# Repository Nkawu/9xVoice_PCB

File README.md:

Circuit board designs for the 9X RC Transmitters mods

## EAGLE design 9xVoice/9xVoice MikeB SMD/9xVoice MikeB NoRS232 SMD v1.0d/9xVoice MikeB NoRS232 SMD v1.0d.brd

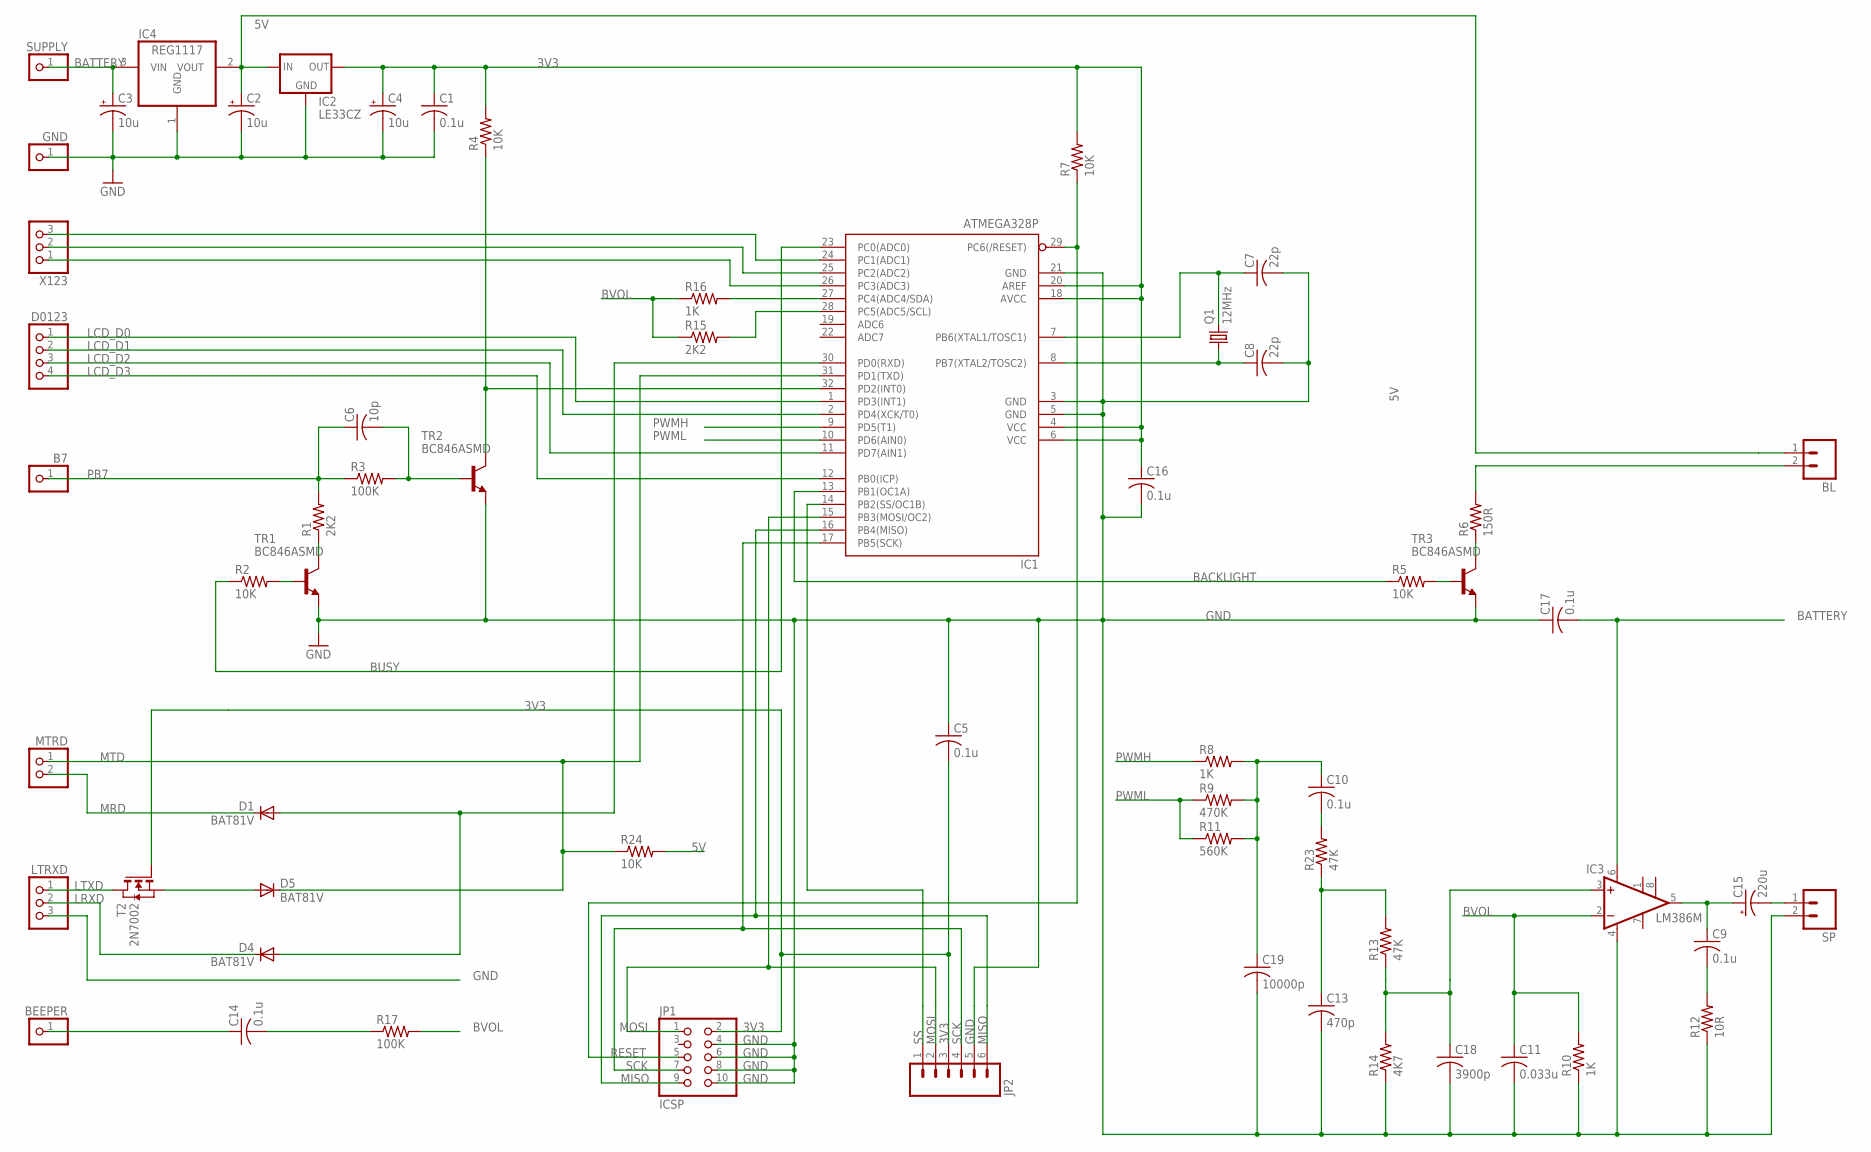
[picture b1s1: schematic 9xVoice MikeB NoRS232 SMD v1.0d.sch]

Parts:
B7: PINHD-1X1; 1X01
BEEPER: PINHD-1X1; 1X01
BL: M02PTH; 1X02
C1, C5, C9, C10, C14, C16, C17: 0.1u; C1206
C2, C3, C4: 10u; A/3216-18R
C6: 10p; C1206
C7, C8: 22p; C1206
C11: 0.033u; C1206
C13: 470p; C1206
C15: 220u; CT7343
C18: 3900p; C1206
C19: 10000p; C1206
D1, D4, D5: BAT81V; SOD123
D0123: PINHD-1X4; 1X04
GND: PINHD-1X1; 1X01
IC1: ATMEGA328P; TQFP32-08; MPN ATMEGA8-16AU
IC2: LE33CZ; SOT23
IC3: LM386M; SO08
IC4: REG1117; SOT223
JP1: ICSP; 2X05
JP2: M06SIP; 1X06
LTRXD: PINHD-1X3; 1X03
MTRD: PINHD-1X2; 1X02
Q1: 12MHz; 2-SMD
R1, R15: 2K2; R1206
R2, R4, R5, R7, R24: 10K; R1206
R3, R17: 100K; R1206
R6: 150R; R1206
R8, R10, R16: 1K; R1206
R9: 470K; R1206
R11: 560K; R1206
R12: 10R; R1206
R13, R23: 47K; R1206
R14: 4K7; R1206
SP: M02PTH; 1X02
SUPPLY: PINHD-1X1; 1X01
T2: 2N7002; SOT-23
TR1, TR2, TR3: BC846ASMD; SOT23
X123: PINHD-1X3; 1X03

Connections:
3V3: C1.1, C4.+, C5.2, C16.1, IC1.4 (VCC), IC1.6 (VCC), IC1.18 (AVCC), IC1.20 (AREF), IC2.2 (OUT), JP1.2, JP2.3, R4.2, R7.2, T2.3 (G)
5V: BL.1, C2.+, IC2.3 (IN), IC4.2 (VOUT), R24.2
BACKLIGHT: IC1.13 (PB1(OC1A)), R5.1
BATTERY: C3.+, C17.2, IC3.6 (VS), IC4.3 (VIN), SUPPLY.1
BEEPER: BEEPER.1, C14.1
BUSY: IC1.23 (PC0(ADC0)), R2.1
BVOL: C11.1, IC3.2 (-IN), R10.2, R15.1, R16.1, R17.2
GND: C1.2, C2.-, C3.-, C4.-, C5.1, C7.2, C8.2, C11.2, C13.2, C16.2, C17.1, C18.2, C19.2, GND.1, IC1.3 (GND), IC1.5 (GND), IC1.21 (GND), IC2.1 (GND), IC3.4 (GND), IC4.1 (GND), JP1.4, JP1.6, JP1.8, JP1.10, JP2.5, LTRXD.3, R10.1, R12.1, R14.1, SP.2, TR1.2 (E), TR2.2 (E), TR3.2 (E)
LCD_D0: D0123.1, IC1.1 (PD3(INT1))
LCD_D1: D0123.2, IC1.2 (PD4(XCK/T0))
LCD_D2: D0123.3, IC1.11 (PD7(AIN1))
LCD_D3: D0123.4, IC1.12 (PB0(ICP))
LRXD: D4.C, LTRXD.2
LTXD: LTRXD.1, T2.1 (D)
MISO: IC1.16 (PB4(MISO)), JP1.9, JP2.6
MOSI: IC1.15 (PB3(MOSI/OC2)), JP1.1, JP2.2
MRD: D1.C, MTRD.2
MTD: D5.C, IC1.31 (PD1(TXD)), MTRD.1, R24.1
unnamed: C13.1, R13.2, R23.1
unnamed: IC1.28 (PC5(ADC5/SCL)), R15.2
unnamed: IC1.27 (PC4(ADC4/SDA)), R16.2
unnamed: D5.A, T2.2 (S)
unnamed: R1.1, TR1.3 (C)
unnamed: R2.2, TR1.1 (B)
unnamed: C6.2, R3.2, TR2.1 (B)
unnamed: C14.2, R17.1
unnamed: R5.2, TR3.1 (B)
unnamed: R6.1, TR3.3 (C)
unnamed: C10.2, R23.2
unnamed: IC1.32 (PD2(INT0)), R4.1, TR2.3 (C)
unnamed: C8.1, IC1.8 (PB7(XTAL2/TOSC2)), Q1.P$1 (1)
unnamed: C7.1, IC1.7 (PB6(XTAL1/TOSC1)), Q1.P$2 (2)
unnamed: BL.2, R6.2
unnamed: C9.1, C15.+, IC3.5 (OUT)
unnamed: C9.2, R12.2
unnamed: C15.-, SP.1
unnamed: C10.1, C19.1, R8.2, R9.2, R11.2
unnamed: C18.1, IC3.3 (+IN), R13.1, R14.2
PB7: B7.1, C6.1, R1.2, R3.1
PWMH: IC1.9 (PD5(T1)), R8.1
PWML: IC1.10 (PD6(AIN0)), R9.1, R11.1
RESET: IC1.29 (PC6(/RESET)), JP1.5, R7.1
RXD: D1.A, D4.A, IC1.30 (PD0(RXD))
SCK: IC1.17 (PB5(SCK)), JP1.7, JP2.4
SS: IC1.14 (PB2(SS/OC1B)), JP2.1
X1: IC1.26 (PC3(ADC3)), X123.1
X2: IC1.25 (PC2(ADC2)), X123.2
X3: IC1.24 (PC1(ADC1)), X123.3

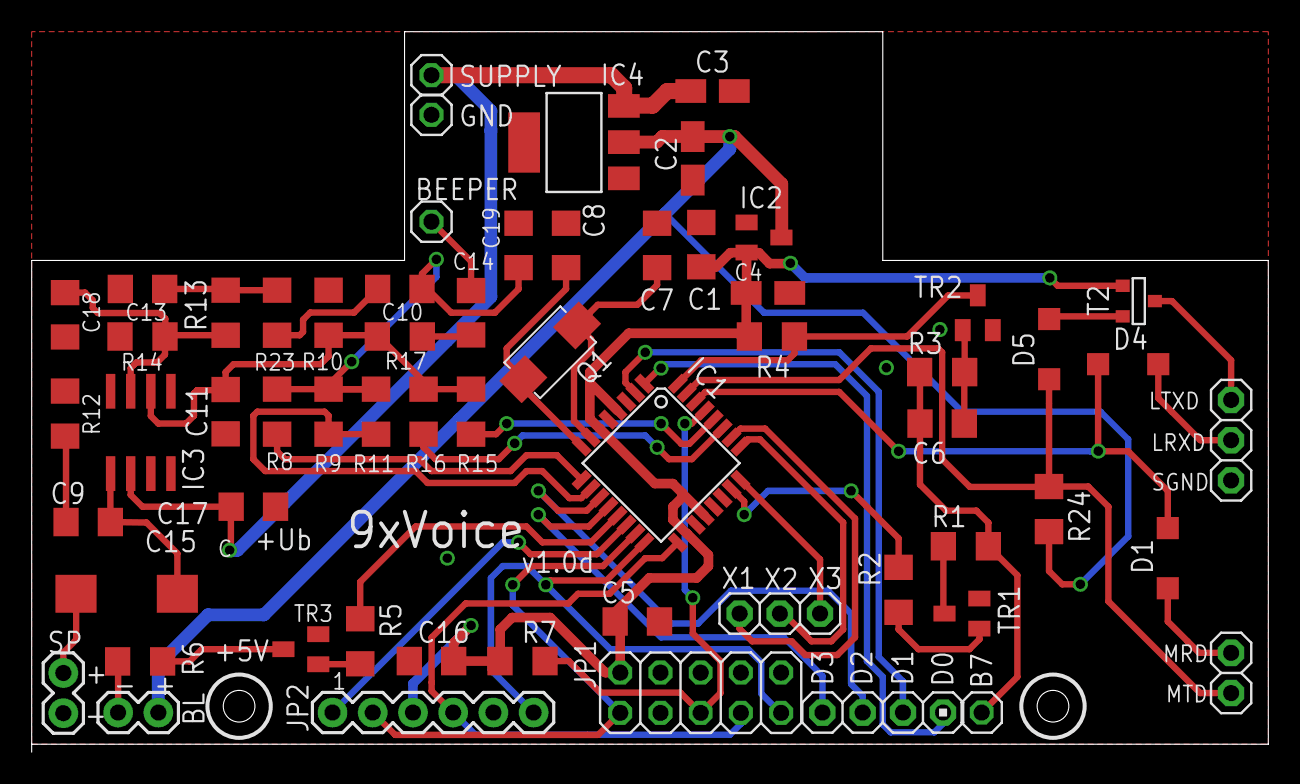
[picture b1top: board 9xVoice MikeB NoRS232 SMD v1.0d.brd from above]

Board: 2 copper layers, 78.1 x 45.5 mm, 61 parts (0 on the bottom side), 48 nets.

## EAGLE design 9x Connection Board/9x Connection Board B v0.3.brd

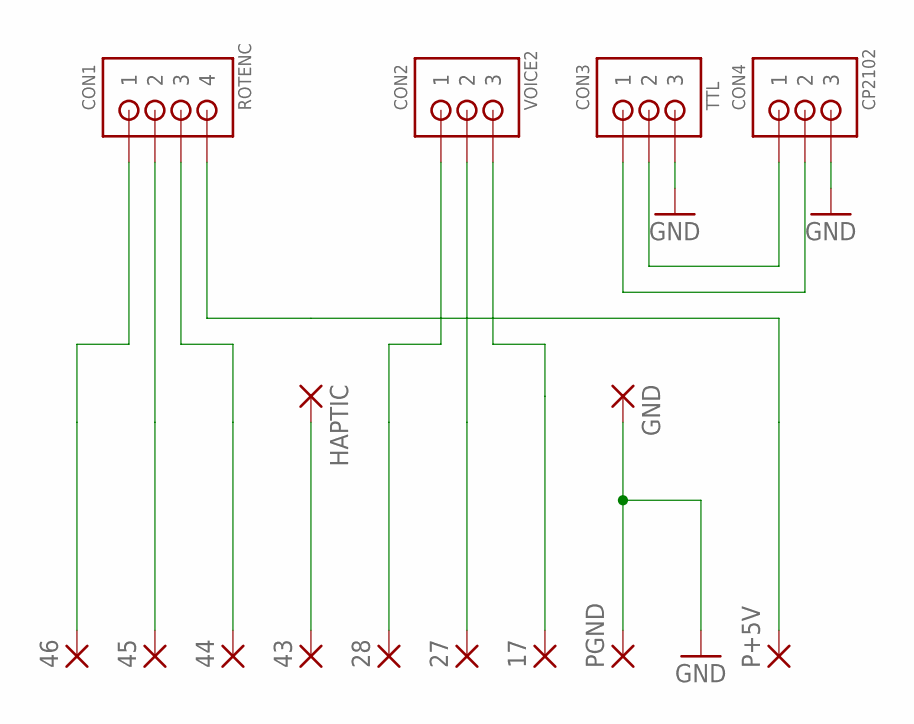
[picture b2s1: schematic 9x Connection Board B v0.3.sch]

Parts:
17, 27, 28, 43, 44, 45, 46: WIREPADSMD1,27-254; SMD1,27-2,54
CON1: ROTENC; B4B-ZR
CON2: VOICE2; B3B-ZR
CON3: TTL; B3B-ZR
CON4: CP2102; B3B-ZR
GND: WIREPADSMD1,27-254; SMD1,27-2,54
HAPTIC: WIREPADSMD1,27-254; SMD1,27-2,54
P+5V: WIREPADSMD1,27-254; SMD1,27-2,54
PGND: WIREPADSMD1,27-254; SMD1,27-2,54

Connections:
GND: CON3.3, CON4.3, GND.1, PGND.1
unnamed: CON3.1, CON4.2
unnamed: CON3.2, CON4.1
unnamed: 43.1, HAPTIC.1
unnamed: CON1.4, P+5V.1
PA5: 46.1, CON1.1
PA6: 45.1, CON1.2
PA7: 44.1, CON1.3
PB7: 17.1, CON2.3
PD2: 27.1, CON2.2
PD3: 28.1, CON2.1

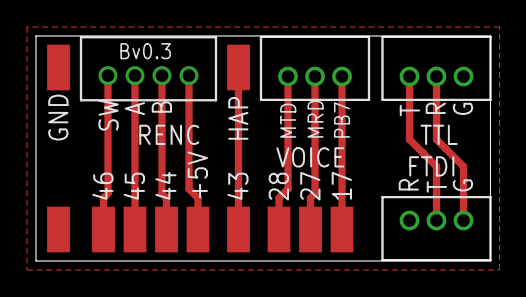
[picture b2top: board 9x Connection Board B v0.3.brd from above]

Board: 2 copper layers, 25.2 x 12.5 mm, 15 parts (0 on the bottom side), 11 nets.

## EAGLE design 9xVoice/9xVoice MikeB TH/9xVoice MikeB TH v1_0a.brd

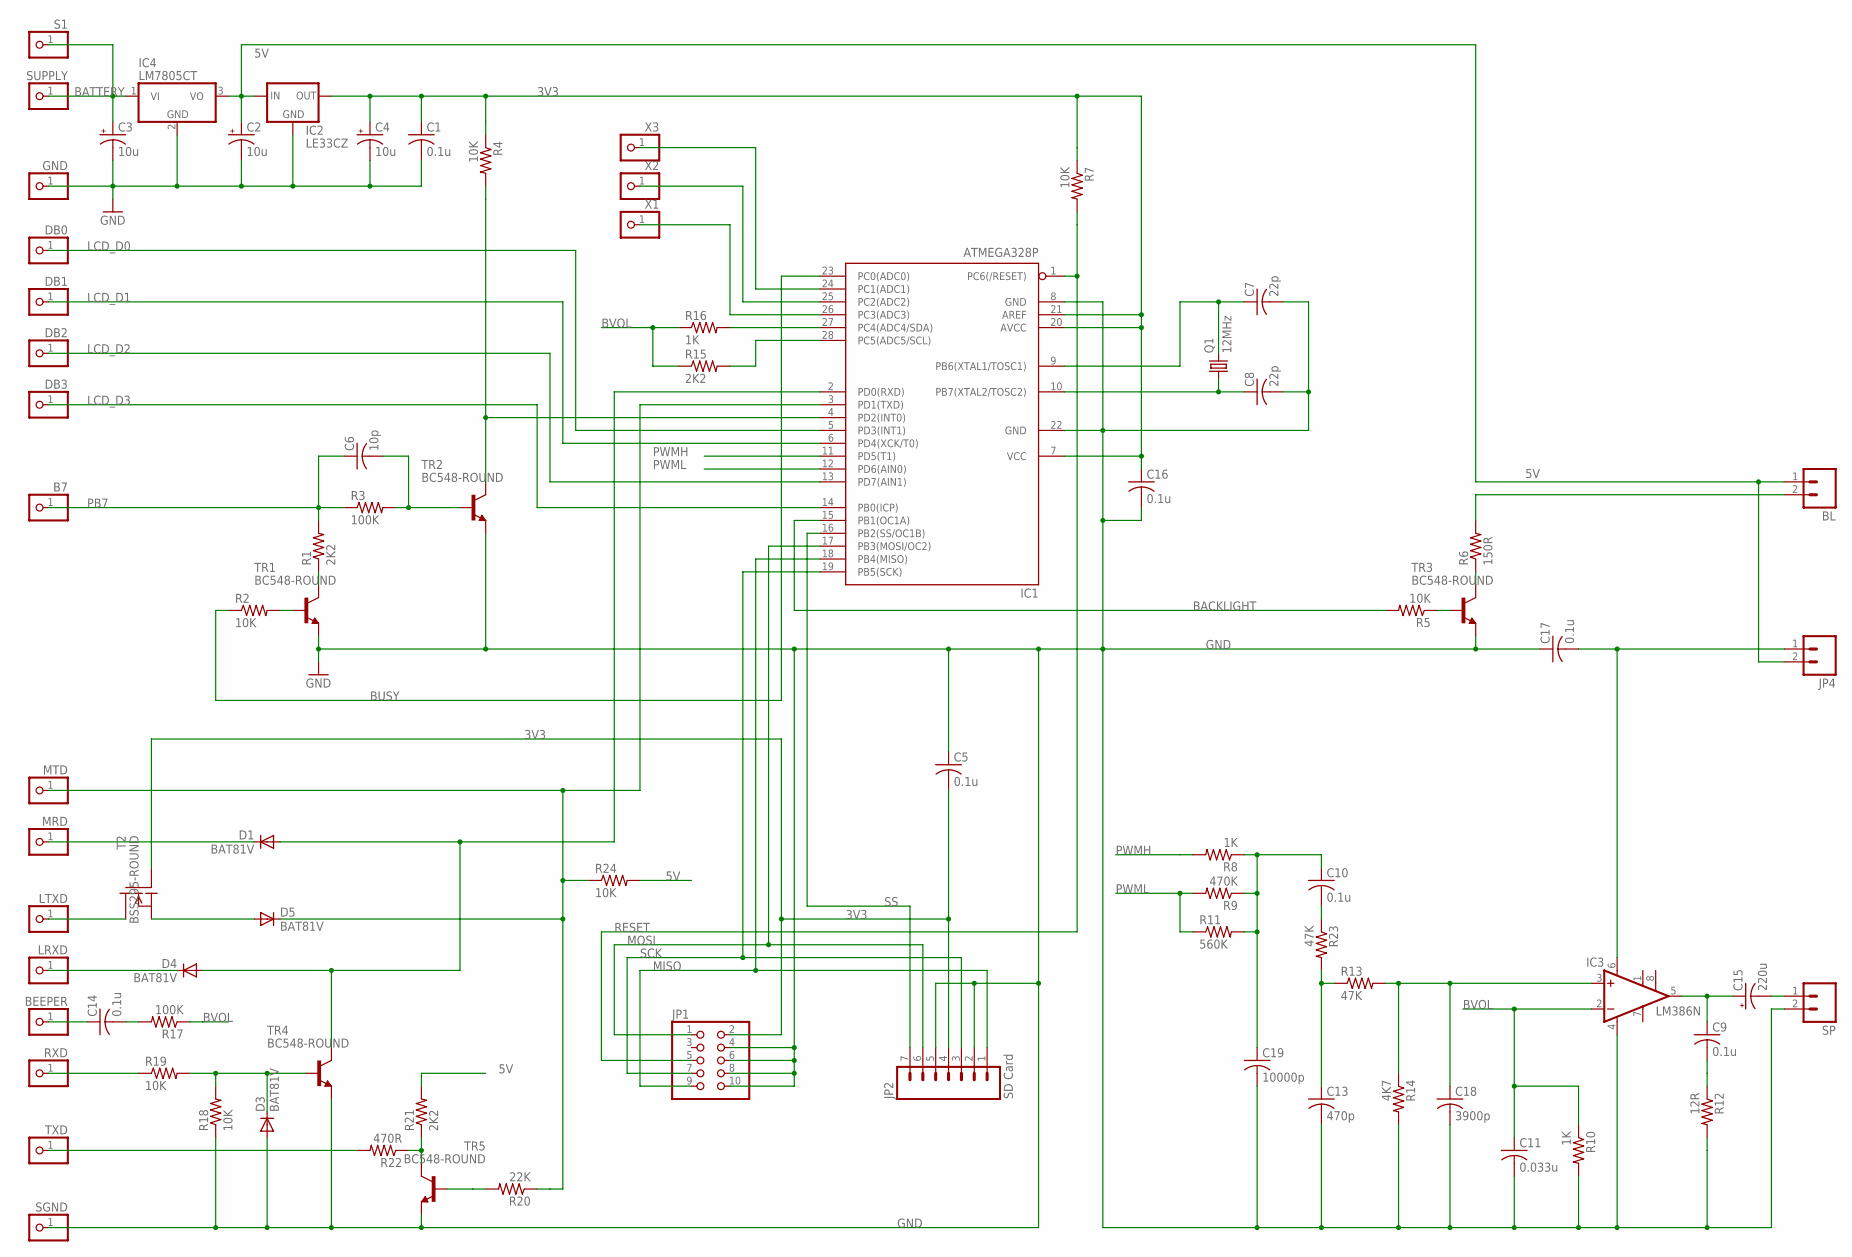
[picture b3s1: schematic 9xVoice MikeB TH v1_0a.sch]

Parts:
B7: PINHD-1X1; 1X01
BEEPER: PINHD-1X1; 1X01
BL: M02PTH; 1X02
C1, C5, C9, C10, C14, C16, C17: 0.1u; C025-024X044
C2, C3, C4: 10u; E2,5-5
C6: 10p; C025-024X044
C7, C8: 22p; C025-024X044
C11: 0.033u; C025-024X044
C13: 470p; C025-024X044
C15: 220u; E5-8,5
C18: 3900p; C025-024X044
C19: 10000p; C025-024X044
D1, D3, D4, D5: BAT81V; D-2.5
DB0, DB1, DB2, DB3: PINHD-1X1; 1X01
GND: PINHD-1X1; 1X01
IC1: ATMEGA328P; DIL28-3-JDC
IC2: LE33CZ; TO92-JDC
IC3: LM386N; DIL08
IC4: LM7805CT; TO220H
JP1: PINHD-2X5; 2X05
JP2: SD Card; 1X07
JP4: M02PTH; 1X02
LRXD: PINHD-1X1; 1X01
LTXD: PINHD-1X1; 1X01
MRD: PINHD-1X1; 1X01
MTD: PINHD-1X1; 1X01
Q1: 12MHz; HC49US
R1, R15, R21: 2K2; 0207/2V
R2: 10K; 0204/7
R3, R17: 100K; 0207/2V
R4, R5, R7, R18, R19, R24: 10K; 0207/2V
R6: 150R; 0207/2V
R8, R10, R16: 1K; 0207/2V
R9: 470K; 0207/2V
R11: 560K; 0207/2V
R12: 12R; 0207/2V
R13, R23: 47K; 0207/2V
R14: 4K7; 0207/2V
R20: 22K; 0207/2V
R22: 470R; 0207/2V
RXD: PINHD-1X1; 1X01
S1: PINHD-1X1; 1X01
SGND: PINHD-1X1; 1X01
SP: M02PTH; 1X02
SUPPLY: PINHD-1X1; 1X01
T2: BSS295-ROUND; TO92-JDC
TR1, TR2, TR3, TR4, TR5: BC548-ROUND; TO92-JDC
TXD: PINHD-1X1; 1X01
X1, X2, X3: PINHD-1X1; 1X01

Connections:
3V3: C1.1, C4.+, C5.2, C16.1, IC1.7 (VCC), IC1.20 (AVCC), IC1.21 (AREF), IC2.C (OUT), JP1.2, JP2.4, R4.1, R7.1, T2.B (G)
5V: BL.1, C2.+, IC2.E (IN), IC4.3 (VO), JP4.2, R21.2, R24.2
BACKLIGHT: IC1.15 (PB1(OC1A)), R5.2
BATTERY: C3.+, IC4.1 (VI), S1.1, SUPPLY.1
BUSY: IC1.23 (PC0(ADC0)), R2.1
BVOL: C11.1, IC3.2 (-IN), R10.1, R15.1, R16.1, R17.1
GND: C1.2, C2.-, C3.-, C4.-, C5.1, C7.2, C8.2, C11.2, C13.2, C16.2, C17.1, C18.2, C19.2, D3.A, GND.1, IC1.8 (GND), IC1.22 (GND), IC2.B (GND), IC3.4 (GND), IC4.2 (GND), JP1.4, JP1.6, JP1.8, JP1.10, JP2.2, JP2.5, R10.2, R12.2, R14.2, R18.1, SGND.1, SP.2, TR1.E, TR2.E, TR3.E, TR4.E, TR5.E
LCD_D0: DB0.1, IC1.5 (PD3(INT1))
LCD_D1: DB1.1, IC1.6 (PD4(XCK/T0))
LCD_D2: DB2.1, IC1.13 (PD7(AIN1))
LCD_D3: DB3.1, IC1.14 (PB0(ICP))
MISO: IC1.18 (PB4(MISO)), JP1.9, JP2.1
MOSI: IC1.17 (PB3(MOSI/OC2)), JP1.1, JP2.6
unnamed: C13.1, R13.1, R23.2
unnamed: R21.1, R22.1, TR5.C
unnamed: R22.2, TXD.1
unnamed: R20.2, TR5.B
unnamed: IC1.28 (PC5(ADC5/SCL)), R15.2
unnamed: IC1.27 (PC4(ADC4/SDA)), R16.2
unnamed: IC1.26 (PC3(ADC3)), X1.1
unnamed: IC1.25 (PC2(ADC2)), X2.1
unnamed: IC1.24 (PC1(ADC1)), X3.1
unnamed: R19.1, RXD.1
unnamed: D3.C, R18.2, R19.2, TR4.B
unnamed: D4.C, LRXD.1
unnamed: D5.A, T2.C (S)
unnamed: LTXD.1, T2.E (D)
unnamed: D1.C, MRD.1
unnamed: R1.1, TR1.C
unnamed: R2.2, TR1.B
unnamed: C6.2, R3.2, TR2.B
unnamed: BEEPER.1, C14.1
unnamed: C14.2, R17.2
unnamed: R5.1, TR3.B
unnamed: R6.1, TR3.C
unnamed: C10.2, R23.1
unnamed: IC1.4 (PD2(INT0)), R4.2, TR2.C
unnamed: C8.1, IC1.10 (PB7(XTAL2/TOSC2)), Q1.1
unnamed: C7.1, IC1.9 (PB6(XTAL1/TOSC1)), Q1.2
unnamed: BL.2, R6.2
unnamed: C9.1, C15.+, IC3.5 (OUT)
unnamed: C9.2, R12.1
unnamed: C15.-, SP.1
unnamed: C17.2, IC3.6 (VS), JP4.1
unnamed: C10.1, C19.1, R8.1, R9.1, R11.2
unnamed: C18.1, IC3.3 (+IN), R13.2, R14.1
PB7: B7.1, C6.1, R1.2, R3.1
PWMH: IC1.11 (PD5(T1)), R8.2
PWML: IC1.12 (PD6(AIN0)), R9.2, R11.1
RESET: IC1.1 (PC6(/RESET)), JP1.5, R7.2
RXD: D1.A, D4.A, IC1.2 (PD0(RXD)), TR4.C
SCK: IC1.19 (PB5(SCK)), JP1.7, JP2.3
SS: IC1.16 (PB2(SS/OC1B)), JP2.7
TXD: D5.C, IC1.3 (PD1(TXD)), MTD.1, R20.1, R24.1

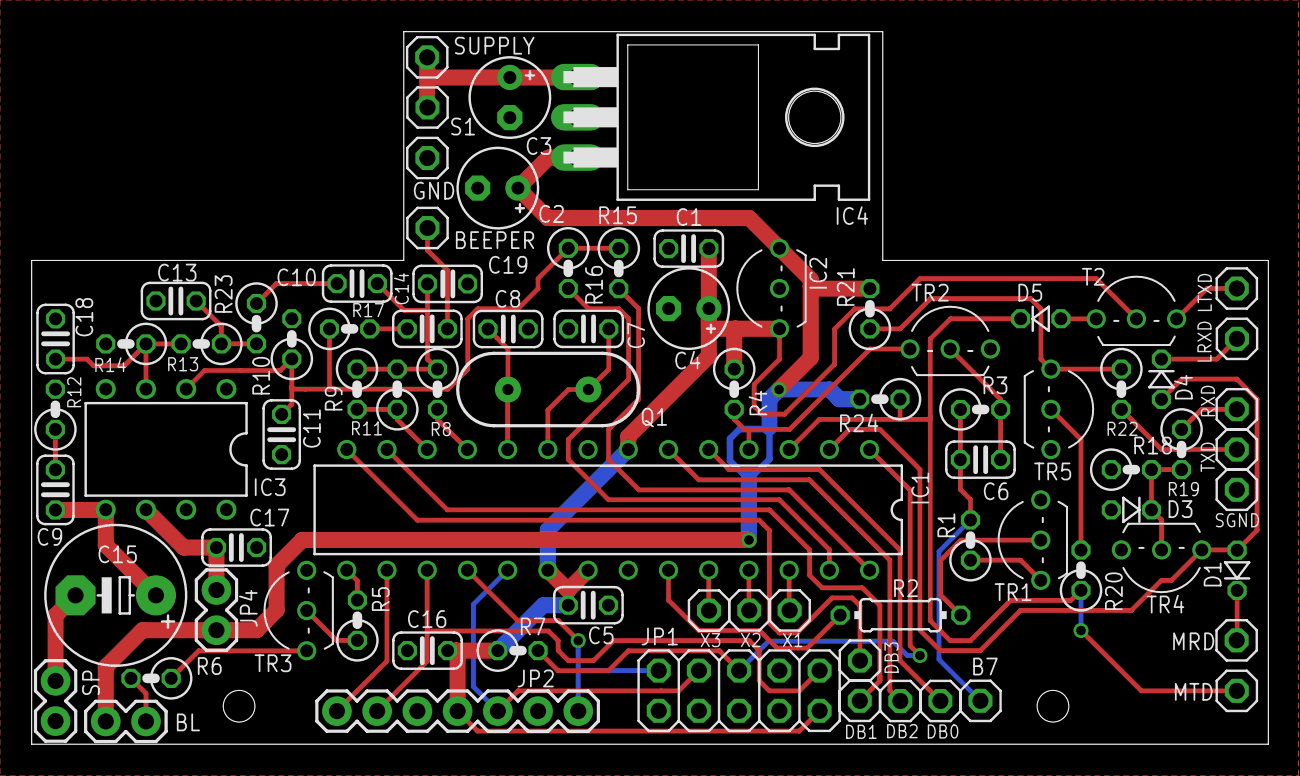
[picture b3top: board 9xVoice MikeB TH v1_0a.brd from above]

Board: 2 copper layers, 78.1 x 45.0 mm, 81 parts (0 on the bottom side), 54 nets.

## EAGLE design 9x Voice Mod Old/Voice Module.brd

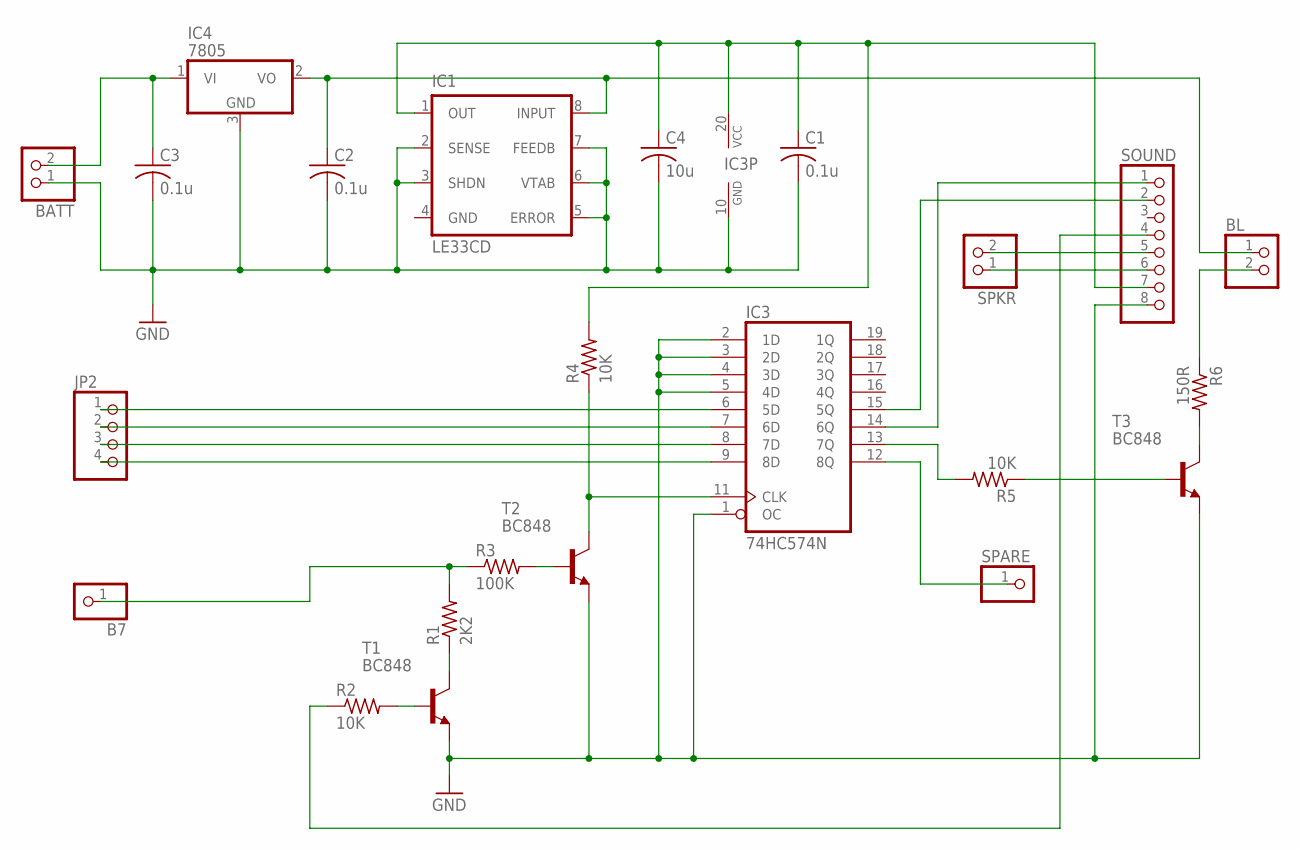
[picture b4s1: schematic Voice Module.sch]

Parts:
B7: PINHD-1X1; 1X01
BATT: PINHD-1X2; 1X02
BL: PINHD-1X2; 1X02
C1, C2, C3: 0.1u; C1206
C4: 10u; C1206
IC1: LE33CD; SO-08
IC3: 74HC574N; SO20W
IC4: 7805; TO252
JP2: PINHD-1X4; 1X04
R1: 2K2; R1206
R2, R4, R5: 10K; R1206
R3: 100K; R1206
R6: 150R; R1206
SOUND: PINHD-1X8; 1X08
SPARE: PINHD-1X1; 1X01
SPKR: PINHD-1X2; 1X02
T1, T2, T3: BC848; SOT23

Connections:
3V3: C1.1, C4.1, IC1.1 (OUT), IC3.20 (VCC), R4.2, SOUND.7
5V: BL.1, C2.1, IC1.8 (INPUT), IC4.2 (VO)
BACKLIGHT: IC3.13 (7Q), R5.2
BATTERY: BATT.2, C3.1, IC4.1 (VI)
BUSY: R2.1, SOUND.4
CLK_AUDIO: IC3.14 (6Q), SOUND.1
DATA_AUDIO: IC3.15 (5Q), SOUND.2
GND: BATT.1, C1.2, C2.2, C3.2, C4.2, IC1.2 (SENSE), IC1.3 (SHDN), IC1.4 (GND), IC1.5 (ERROR), IC1.6 (VTAB), IC1.7 (FEEDB), IC3.1 (OC), IC3.2 (1D), IC3.3 (2D), IC3.4 (3D), IC3.5 (4D), IC3.10 (GND), IC4.3 (GND), SOUND.8, T1.2 (E), T2.2 (E), T3.2 (E)
LCD_D0: IC3.6 (5D), JP2.1
LCD_D1: IC3.7 (6D), JP2.2
LCD_D2: IC3.8 (7D), JP2.3
LCD_D3: IC3.9 (8D), JP2.4
unnamed: R2.2, T1.1 (B)
unnamed: R1.1, T1.3 (C)
unnamed: R3.2, T2.1 (B)
unnamed: IC3.11 (CLK), R4.1, T2.3 (C)
unnamed: R5.1, T3.1 (B)
unnamed: R6.2, T3.3 (C)
unnamed: SOUND.6, SPKR.1
unnamed: BL.2, R6.1
unnamed: SOUND.5, SPKR.2
PB7: B7.1, R1.2, R3.1
SPARE: IC3.12 (8Q), SPARE.1

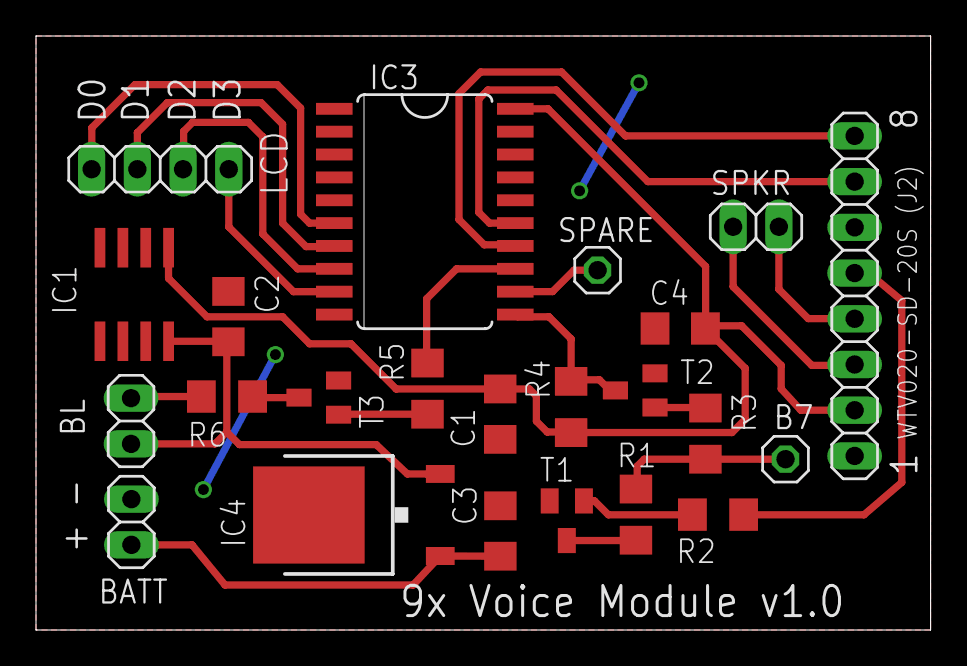
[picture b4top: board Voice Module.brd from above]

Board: 2 copper layers, 49.7 x 33.0 mm, 23 parts (0 on the bottom side), 23 nets.

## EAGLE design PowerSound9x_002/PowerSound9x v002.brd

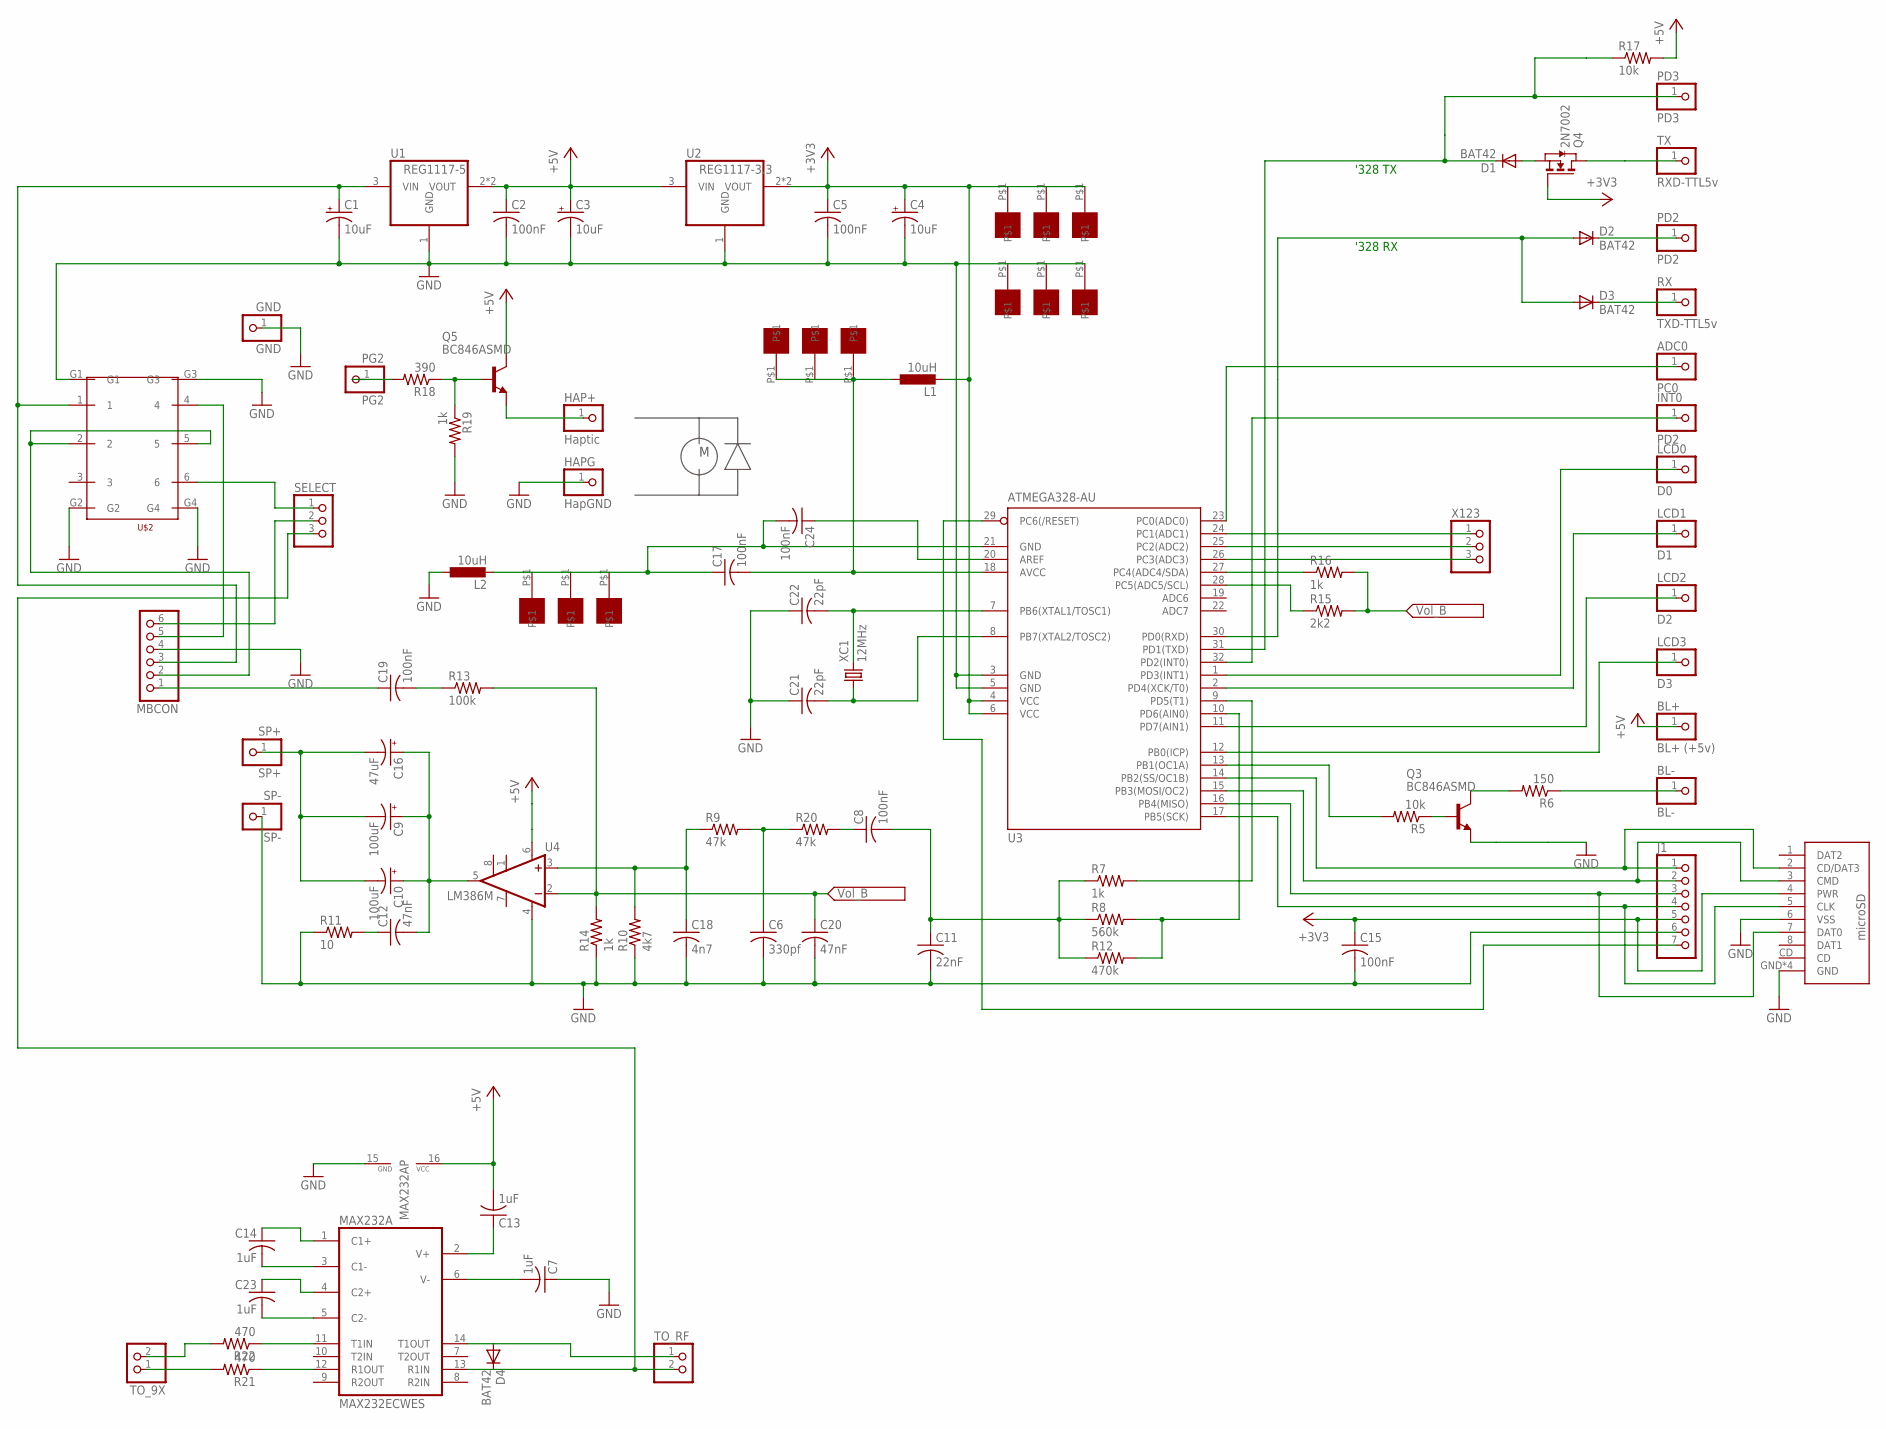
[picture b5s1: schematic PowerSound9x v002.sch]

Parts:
ADC0: PC0; 1X01
BL+: BL+ (+5v); 1X01
BL-: BL-; 1X01
C1, C3, C4: 10uF; CT3528
C2, C5, C8, C15, C17, C19, C24: 100nF; C1206
C6: 330pf; C1206
C7, C13, C14, C23: 1uF; C1206
C9, C10: 100uF; CT6032
C11: 22nF; C1206
C12, C20: 47nF; C1206
C16: 47uF; CT6032
C18: 4n7; C1206
C21, C22: 22pF; C1206
D1, D2, D3, D4: BAT42; SOD123
GND: GND; 1X01
HAP+: Haptic; 1X01
HAPG: HapGND; 1X01
INT0: PD2; 1X01
J1: PINHD-1X7; 1X07
L1, L2: 10uH; L3225M
LCD0: D0; 1X01
LCD1: D1; 1X01
LCD2: D2; 1X01
LCD3: D3; 1X01
MAX232A: MAX232ECWES; SO16
MBCON: PINHD-1X6; 1X06
PD2: PD2; 1X01
PD3: PD3; 1X01
PG2: PG2; 1X01
Q3, Q5: BC846ASMD; SOT23
Q4: 2N7002; SOT-23
R5, R17: 10k; R1206
R6: 150; R1206
R7, R14, R16, R19: 1k; R1206
R8: 560k; R1206
R9, R20: 47k; R1206
R10: 4k7; R1206
R11: 10; R1206
R12: 470k; R1206
R13: 100k; R1206
R15: 2k2; R1206
R18: 390; R1206
R21, R22: 470; R1206
RX: TXD-TTL5v; 1X01
SELECT: PINHD-1X3; 1X03
SP+: SP+; 1X01
SP-: SP-; 1X01
TO_9X: PINHD-1X2; 1X02
TO_RF: PINHD-1X2; 1X02
TX: RXD-TTL5v; 1X01
U1: REG1117-5; SOT223
U2: REG1117-3.3; SOT223
U3: ATMEGA328-AU; TQFP32-08
U4: LM386M; SO08
U$1, U$4, U$5, U$6, U$7, U$8, U$9, U$10, U$11, U$12, U$13, U$14: PAD
U$2: SS22H02SS22H02; SS22H02
U$3: 112J-TDAR-R
X123: PINHD-1X3; 1X03
XC1: 12MHz; HC49UP

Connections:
+5V: BL+.1, C2.1, C3.+, C13.2, MAX232A.16 (VCC), Q5.3 (C), R17.2, U1.2 (VOUT), U1.4 (VOUT), U2.3 (VIN), U4.6 (VS)
B7: INT0.1, U3.32 (PD2(INT0))
GND: C1.-, C2.2, C3.-, C4.-, C5.2, C6.2, C7.1, C11.2, C15.2, C18.2, C20.2, C21.1, C22.1, GND.1, HAPG.1, J1.6, L2.1, MAX232A.15 (GND), MBCON.4, Q3.2 (E), R10.1, R11.1, R14.1, R19.2, SP-.1, U1.1 (GND), U2.1 (GND), U3.3 (GND), U3.5 (GND), U4.4 (GND), U$2.G1, U$2.G2, U$2.G3, U$2.G4, U$3.6 (VSS), U$3.GND, U$3.GND1 (GND), U$3.GND2 (GND), U$3.GND3 (GND), U$12.P$1, U$13.P$1, U$14.P$1
unnamed: ADC0.1, U3.23 (PC0(ADC0))
unnamed: HAP+.1, Q5.2 (E)
unnamed: J1.2, U3.15 (PB3(MOSI/OC2)), U$3.3 (CMD)
unnamed: J1.3, U3.16 (PB4(MISO)), U$3.7 (DAT0)
unnamed: MAX232A.11 (T1IN), R22.1
unnamed: C22.2, U3.7 (PB6(XTAL1/TOSC1)), XC1.2
unnamed: C21.2, U3.8 (PB7(XTAL2/TOSC2)), XC1.1
unnamed: MAX232A.12 (R1OUT), R21.1
unnamed: R16.1, U3.27 (PC4(ADC4/SDA))
unnamed: R15.1, U3.28 (PC5(ADC5/SCL))
unnamed: MBCON.6, SELECT.2
unnamed: SELECT.1, U$2.6
unnamed: C17.2, L1.1, U3.18 (AVCC), U$1.P$1, U$4.P$1, U$5.P$1
unnamed: C9.-, C10.-, C16.-, SP+.1
unnamed: C12.1, R11.2
unnamed: C9.+, C10.+, C12.2, C16.+, U4.5 (OUT)
unnamed: C18.1, R9.1, R10.2, U4.3 (+IN)
unnamed: C19.1, MBCON.1
unnamed: C19.2, R13.1
unnamed: J1.1, U3.14 (PB2(SS/OC1B)), U$3.2 (CD/DAT3)
unnamed: C24.1, U3.20 (AREF)
unnamed: C6.1, R9.2, R20.1
unnamed: C8.2, C11.1, R7.1, R8.1, R12.1
unnamed: Q3.3 (C), R6.2
unnamed: R7.2, U3.9 (PD5(T1))
unnamed: R8.2, R12.2, U3.10 (PD6(AIN0))
unnamed: BL-.1, R6.1
unnamed: LCD3.1, U3.12 (PB0(ICP))
unnamed: LCD2.1, U3.11 (PD7(AIN1))
unnamed: C1.+, MBCON.3, U1.3 (VIN), U$2.1
unnamed: Q3.1 (B), R5.1
unnamed: R5.2, U3.13 (PB1(OC1A))
unnamed: LCD1.1, U3.2 (PD4(XCK/T0))
unnamed: LCD0.1, U3.1 (PD3(INT1))
unnamed: D3.C, RX.1
unnamed: D1.C, PD3.1, R17.1, U3.31 (PD1(TXD))
unnamed: D2.C, PD2.1
unnamed: PG2.1, R18.2
unnamed: Q4.1 (D), TX.1
unnamed: D2.A, D3.A, U3.30 (PD0(RXD))
unnamed: Q5.1 (B), R18.1, R19.1
unnamed: C17.1, C24.2, L2.2, U3.21 (GND), U$6.P$1, U$7.P$1, U$8.P$1
unnamed: D1.A, Q4.2 (S)
unnamed: J1.7, U3.29 (PC6(/RESET))
unnamed: J1.4, U3.17 (PB5(SCK)), U$3.5 (CLK)
unnamed: C4.+, C5.1, C15.1, J1.5, L1.2, Q4.3 (G), U2.2 (VOUT), U2.4 (VOUT), U3.4 (VCC), U3.6 (VCC), U$3.4 (PWR), U$9.P$1, U$10.P$1, U$11.P$1
unnamed: C8.1, R20.2
unnamed: D4.A, MAX232A.14 (T1OUT), TO_RF.1
unnamed: U3.24 (PC1(ADC1)), X123.1
unnamed: U3.25 (PC2(ADC2)), X123.2
unnamed: U3.26 (PC3(ADC3)), X123.3
unnamed: MBCON.2, U$2.2, U$2.5
unnamed: MBCON.5, U$2.4
unnamed: D4.C, MAX232A.13 (R1IN), SELECT.3, TO_RF.2
unnamed: R21.2, TO_9X.1
unnamed: R22.2, TO_9X.2
unnamed: C7.2, MAX232A.6 (V-)
unnamed: C23.2, MAX232A.5 (C2-)
unnamed: C23.1, MAX232A.4 (C2+)
unnamed: C14.2, MAX232A.3 (C1-)
unnamed: C14.1, MAX232A.1 (C1+)
unnamed: C13.1, MAX232A.2 (V+)
VOL_B: C20.1, R13.2, R14.2, R15.2, R16.2, U4.2 (-IN)

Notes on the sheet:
'328 RX
'328 TX

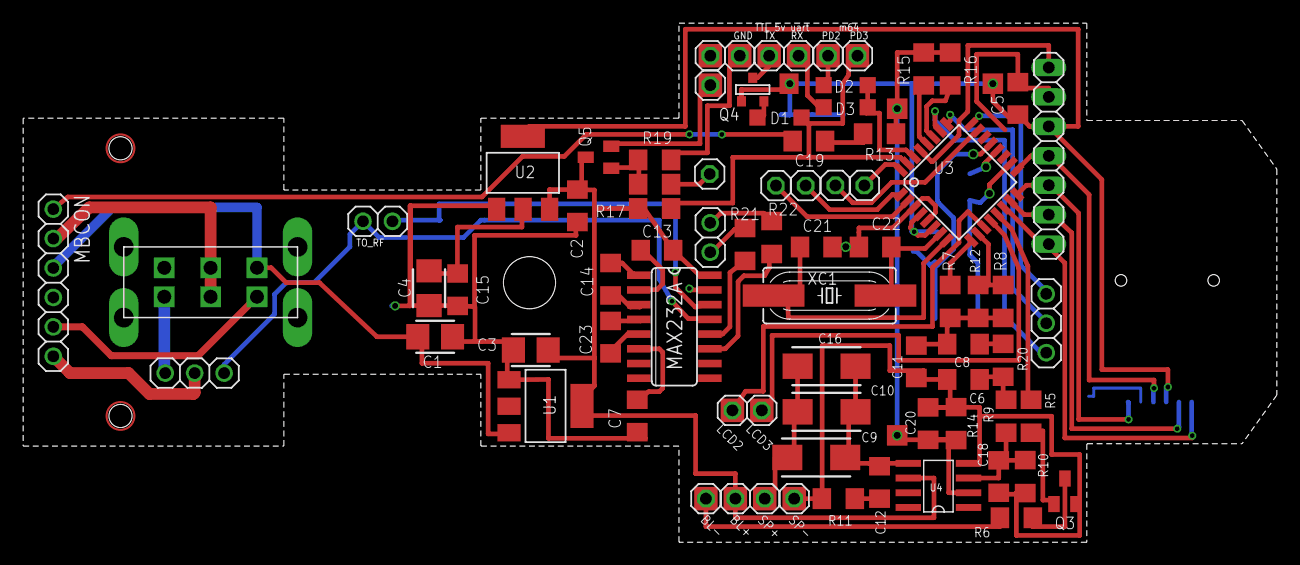
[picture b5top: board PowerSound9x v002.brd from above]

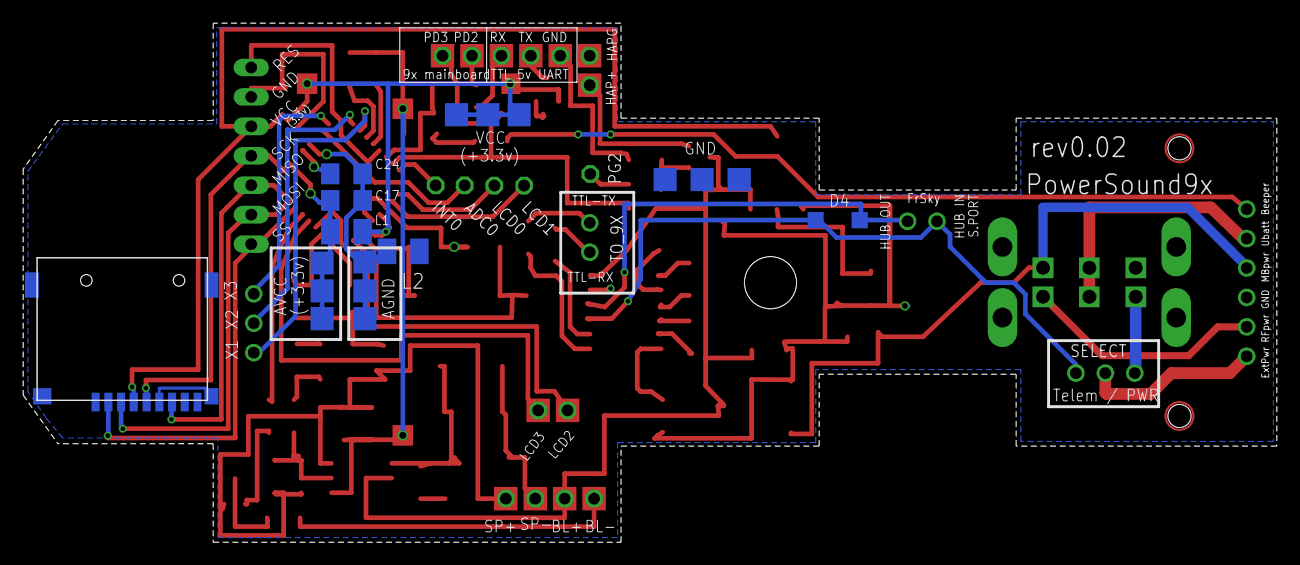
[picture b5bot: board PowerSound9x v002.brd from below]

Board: 2 copper layers, 108.2 x 44.8 mm, 95 parts (18 on the bottom side), 66 nets.

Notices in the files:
parts and their libraries:
SparkFun-Connectors: Licensing: CC v3.0 Share-Alike You are welcome to use this library for commercial purposes.
